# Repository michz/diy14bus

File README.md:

diy14bus
========

Getting started
---------------
Please read [Erste (Repository-)Schritte](http://michz.github.io/diy14bus/2014/12/Erste-Repo-Schritte/) (german).

Short version in english:
Please make sure that you have cloned
[our RIOT fork](https://github.com/patkan/RIOT) on the same directory level.

Example:

    /home/user/home-project/diy14bus/   # this repository
    /home/user/home-project/RIOT/       # patkan/RIOT

For compiling arm based binaries you need a fully functional arm-gcc toolchain.
We use [gcc-arm-embedded](https://launchpad.net/~terry.guo/+archive/ubuntu/gcc-arm-embedded).

If you want to run the configuration tool on a Raspberry Pi,
clone the
[RF24](https://github.com/TMRh20/RF24/tree/interrupts)-
Repository and the 
[WebsocketPP](https://github.com/zaphoyd/websocketpp.git)-
Repository into a directory on the same level as the above mentioned.

Your final directory structure should look like this:

    your_project_dir
    |--> diy14bus/
    |--> RIOT/
    |--> RF24/
    |--> websocketpp/

Compiling
---------
Go to application directory (for example `first-test/`) and run `make`.
(No need to build RIOT directly.)

Compiling cowbus-config-server
------------------------------
One special note about the config-server:
This tool depends on a Raspberry Pi and can be compiled there, and *only there*.
(Fancy crosscompiling voodoo possible...)

Before being able to compile cowbus-config-server, you have to compile and install
the RF24 library by changing to the directory RF24 and type:

    make install   # NOTE: perhaps you need sudo ...

This compiles the RF24 library and installs the binary system wide.

Moreover you need at least GCC version 4.7 or 4.8 (we use C++11 language features).

You need Boost library: System, IOStreams, Thread.
On Raspbian you can simply do:

    apt-get install libboost-system-dev libboost-iostreams-dev libboost-thread-dev

License
-------
We will think about it.

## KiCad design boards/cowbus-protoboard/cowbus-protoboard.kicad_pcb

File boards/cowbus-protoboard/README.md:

cowbus protoboard - a prototyping board
=======================================

Core components
---------------
* CPU: [STM32F030C8T6]
* Radio: nrf24l01+
* LDO: [TS5204]
* EEPROM: [24LC04B-I/SN]

On periphery board:
* Temperatur Sensor: [LM 75]
* Buzzer: Some piezo that does not draw more than 25mA and works with 3,3V,
    for example: [EKULIT SMD-P16]
* LED: [LRTB G6TG]

I2C-Bus
-------

This board provides a I2C bus.
Following addresses are reserved:

* 1010xxx (serial EEPROM; where x is either 1 or 0)
* 1001000 (temperature sensor on periphery board)

License
-------
This board is licensed under
[Creative Commons Attribution 4.0 International (CC BY 4.0)](https://creativecommons.org/licenses/by/4.0/)

[STM32F030C8T6]: http://www.digikey.de/product-detail/de/STM32F030C8T6/497-14043-ND/4357252

[EKULIT SMD-P16]: https://www.reichelt.de/Signalakustik/SMD-P16/3/index.html?ACTION=3&GROUPID=6560&ARTICLE=145909&OFFSET=500&WKID=0&
[LM 75]: https://www.reichelt.de/Temperatursensoren/LM-75-SMD/3/index.html?ACTION=3&GROUPID=6672&ARTICLE=49349&SEARCH=i2c%20temperatur%20sensor&OFFSET=500&WKID=0&
[TS5204]: https://www.reichelt.de/ICs-TLC-TSA-/TS-5204-CX33/3/index.html?ACTION=3&GROUPID=5480&ARTICLE=115980&OFFSET=500&WKID=0&
[24LC04B-I/SN]: https://www.reichelt.de/EEPROM-seriell-Microchip/24LC04B-I-SN/3/index.html?ACTION=3&GROUPID=4511&ARTICLE=40074&OFFSET=500&WKID=0&
[LRTB G6TG]: https://www.reichelt.de/SMD-LEDs-Multi-Color/LRTB-G6TG/3/index.html?ACTION=3&GROUPID=3036&ARTICLE=65109&OFFSET=500&WKID=0&

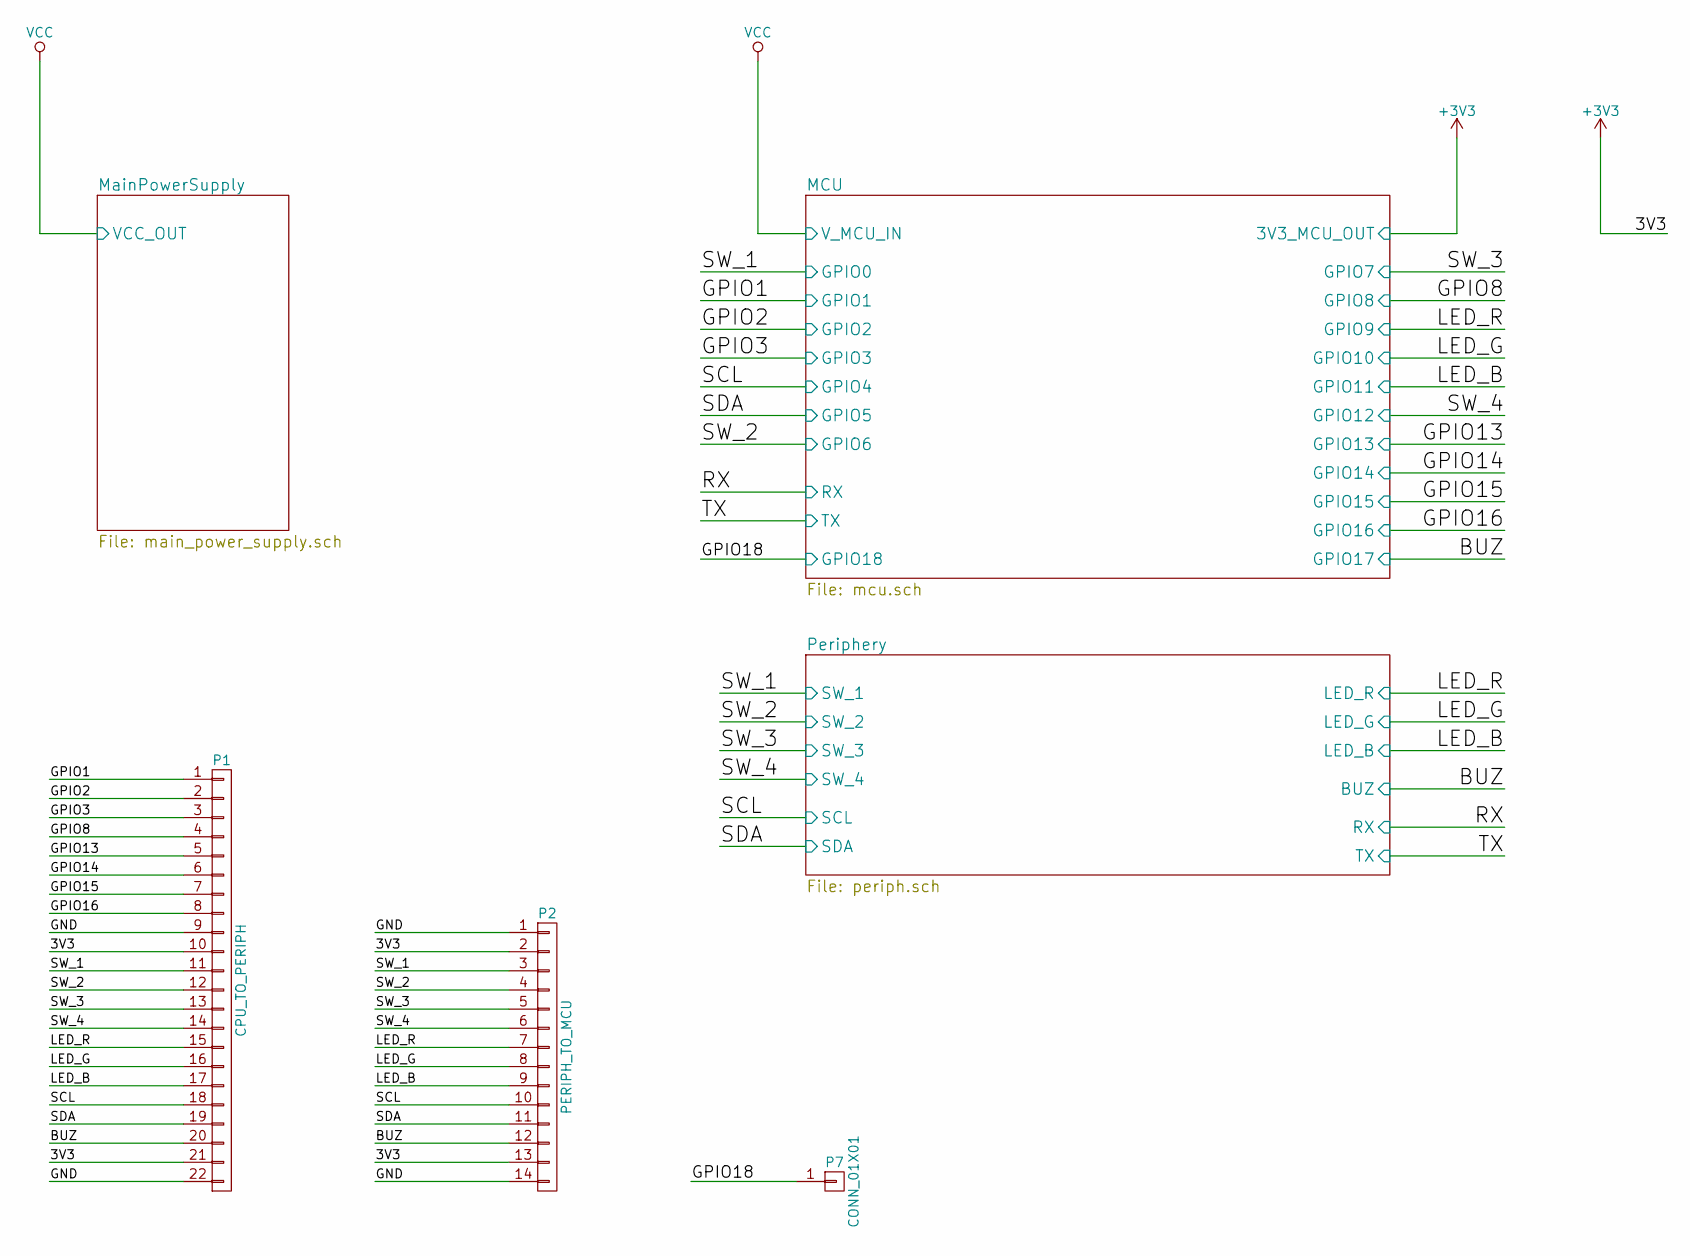
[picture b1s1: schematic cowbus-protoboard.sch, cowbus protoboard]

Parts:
P1: CPU_TO_PERIPH; Pin_Header_Straight_1x22
P2: PERIPH_TO_MCU; Pin_Header_Straight_1x14
P7: CONN_01X01; Pin_Header_Straight_1x01

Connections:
+3V3: P1.10, P1.21, P2.2, P2.13; also elsewhere on the board
/MCU/GPIO0: P1.11, P2.3; also elsewhere on the board
/MCU/GPIO1: P1.1; also elsewhere on the board
/MCU/GPIO2: P1.2; also elsewhere on the board
/MCU/GPIO3: P1.3; also elsewhere on the board
/MCU/GPIO4: P1.18, P2.10; also elsewhere on the board
/MCU/GPIO5: P1.19, P2.11; also elsewhere on the board
/MCU/GPIO6: P1.12, P2.4; also elsewhere on the board
/MCU/GPIO7: P1.13, P2.5; also elsewhere on the board
/MCU/GPIO8: P1.4; also elsewhere on the board
/MCU/GPIO9: P1.15, P2.7; also elsewhere on the board
/MCU/GPIO10: P1.16, P2.8; also elsewhere on the board
/MCU/GPIO11: P1.17, P2.9; also elsewhere on the board
/MCU/GPIO12: P1.14, P2.6; also elsewhere on the board
/MCU/GPIO13: P1.5; also elsewhere on the board
/MCU/GPIO14: P1.6; also elsewhere on the board
/MCU/GPIO15: P1.7; also elsewhere on the board
/MCU/GPIO16: P1.8; also elsewhere on the board
/Periphery/BUZ: P1.20, P2.12; also elsewhere on the board
GND: P1.9, P1.22, P2.1, P2.14; also elsewhere on the board

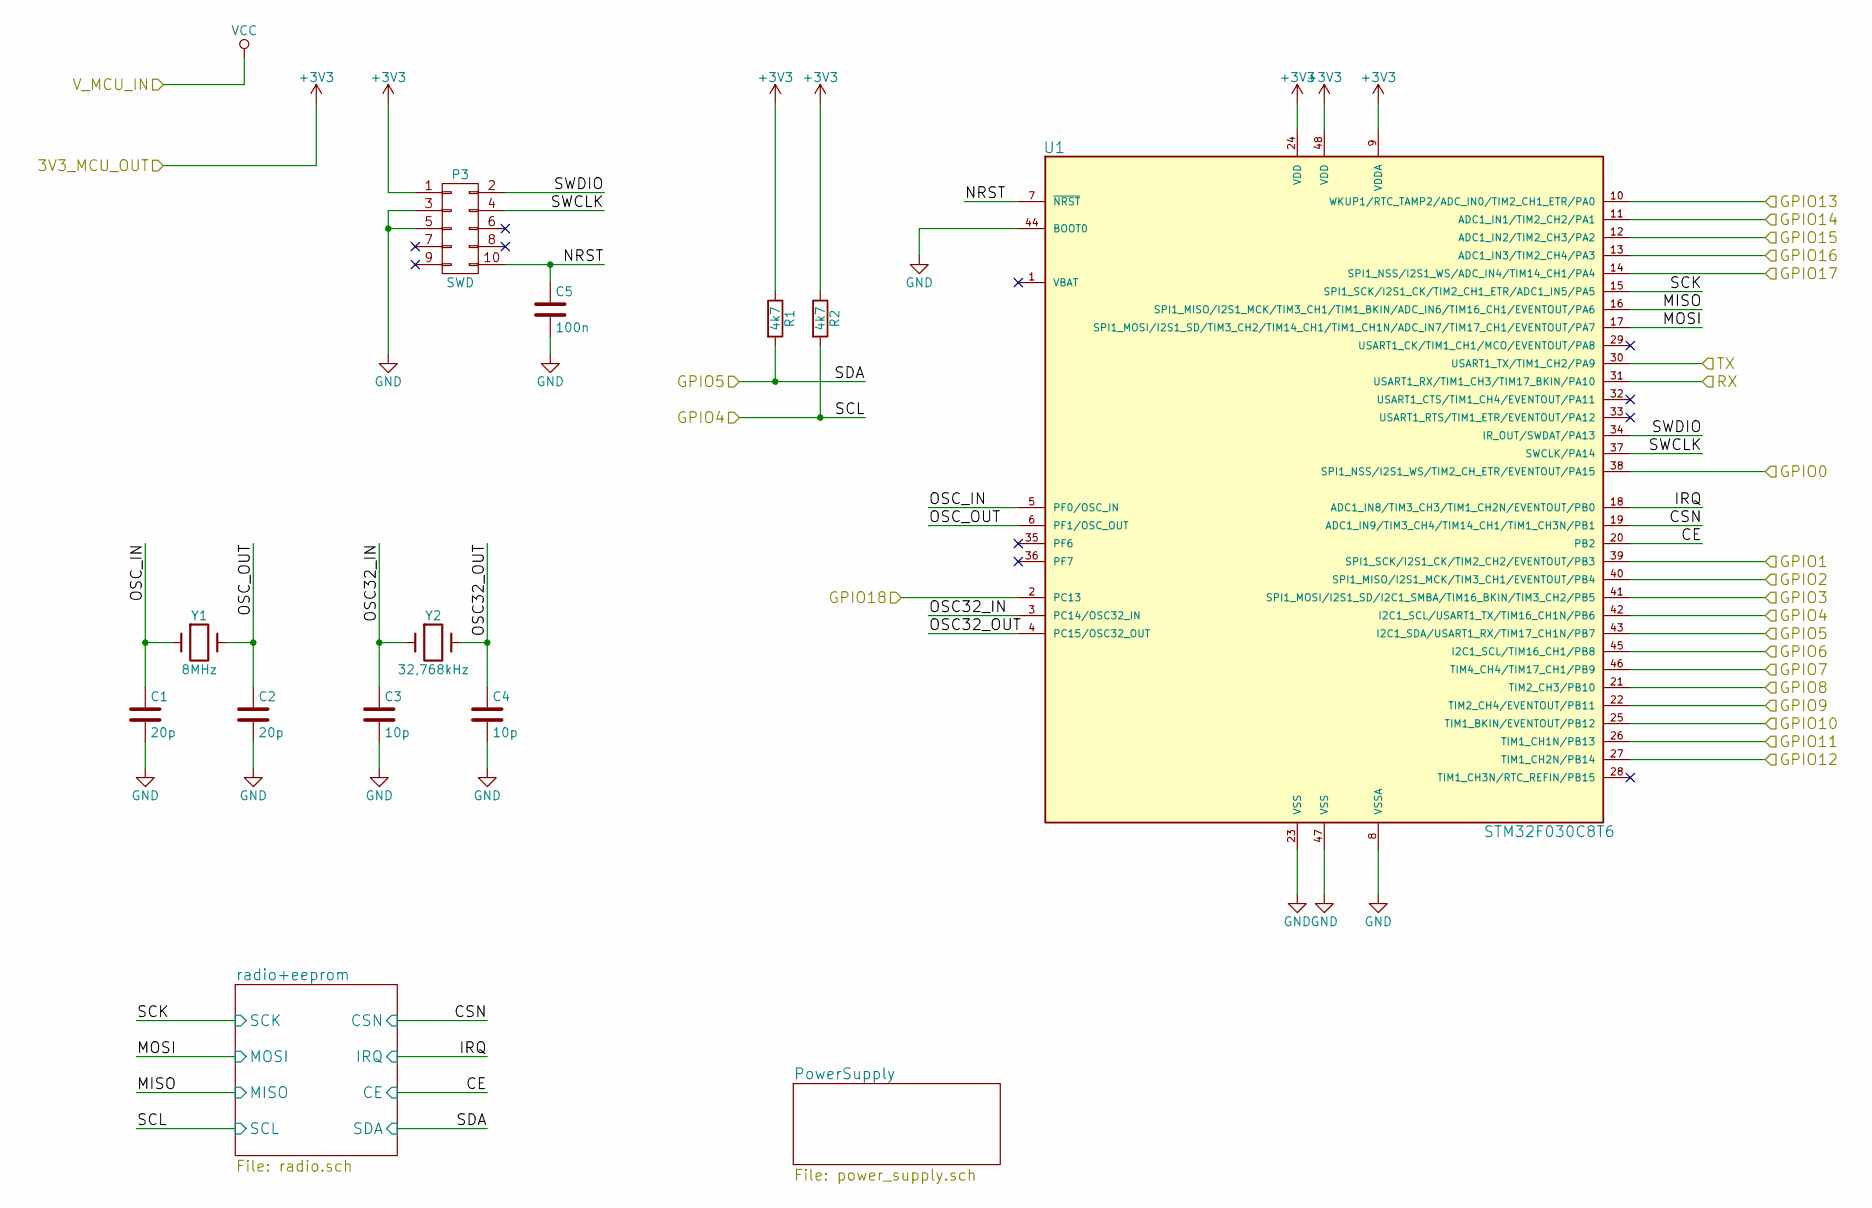
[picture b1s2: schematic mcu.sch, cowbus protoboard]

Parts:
C1, C2: 20p; C_0805_HandSoldering
C3, C4: 10p; C_0805_HandSoldering
C5: 100n; C_0805_HandSoldering
P3: SWD; CORTEX_header_SMD
R1, R2: 4k7; R_0805_HandSoldering
U1: STM32F030C8T6; LQFP-48_7x7mm_Pitch0.5mm
Y1: 8MHz; Crystal_HC49-SD_SMD
Y2: 32,768kHz; crystal_SMD_CPFB

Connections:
+3V3: P3.1, R1.1, R2.1, U1.9 (VDDA), U1.24 (VDD), U1.48 (VDD); also elsewhere on the board
/MCU/GPIO0: U1.38 (SPI1_NSS/I2S1_WS/TIM2_CH_ETR/EVENTOUT/P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); also elsewhere on the board
/MCU/GPIO1: U1.39 (SPI1_SCK/I2S1_CK/TIM2_CH2/EVENTOUT/PB3); also elsewhere on the board
/MCU/GPIO2: U1.40 (SPI1_MISO/I2S1_MCK/TIM3_CH1/EVENTOUT/PB4); also elsewhere on the board
/MCU/GPIO3: U1.41 (SPI1_MOSI/I2S1_SD/I2C1_SMBA/TIM16_BKIN/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); also elsewhere on the board
/MCU/GPIO4: R2.2, U1.42 (I2C1_SCL/USART1_TX/TIM16_CH1N/PB6); also elsewhere on the board
/MCU/GPIO5: R1.2, U1.43 (I2C1_SDA/USART1_RX/TIM17_CH1N/PB7); also elsewhere on the board
/MCU/GPIO6: U1.45 (I2C1_SCL/TIM16_CH1/PB8); also elsewhere on the board
/MCU/GPIO7: U1.46 (TIM4_CH4/TIM17_CH1/PB9); also elsewhere on the board
/MCU/GPIO8: U1.21 (TIM2_CH3/PB10); also elsewhere on the board
/MCU/GPIO9: U1.22 (TIM2_CH4/EVENTOUT/PB11); also elsewhere on the board
/MCU/GPIO10: U1.25 (TIM1_BKIN/EVENTOUT/PB12); also elsewhere on the board
/MCU/GPIO11: U1.26 (TIM1_CH1N/PB13); also elsewhere on the board
/MCU/GPIO12: U1.27 (TIM1_CH2N/PB14); also elsewhere on the board
/MCU/GPIO13: U1.10 (WKUP1/RTC_TAMP2/ADC_IN0/TIM2_CH1_ETR/PA0); also elsewhere on the board
/MCU/GPIO14: U1.11 (ADC1_IN1/TIM2_CH2/PA1); also elsewhere on the board
/MCU/GPIO15: U1.12 (ADC1_IN2/TIM2_CH3/PA2); also elsewhere on the board
/MCU/GPIO16: U1.13 (ADC1_IN3/TIM2_CH4/PA3); also elsewhere on the board
/MCU/GPIO18: U1.2 (PC13); also elsewhere on the board
/MCU/NRST: C5.1, P3.10, U1.7 (~NRST)
/MCU/OSC32_IN: C3.1, U1.3 (PC14/OSC32_IN), Y2.1
/MCU/OSC32_OUT: C4.1, U1.4 (PC15/OSC32_OUT), Y2.2
/MCU/OSC_IN: C1.1, U1.5 (PF0/OSC_IN), Y1.1
/MCU/OSC_OUT: C2.1, U1.6 (PF1/OSC_OUT), Y1.2
/MCU/RX: U1.31 (USART1_RX/TIM1_CH3/TIM17_BKIN/PA10); also elsewhere on the board
/MCU/SWCLK: P3.4, U1.37 (SWCLK/PA14)
/MCU/SWDIO: P3.2, U1.34 (IR_OUT/SWDAT/PA13)
/MCU/TX: U1.30 (USART1_TX/TIM1_CH2/PA9); also elsewhere on the board
/MCU/radio+eeprom/CE: U1.20 (PB2); also elsewhere on the board
/MCU/radio+eeprom/CSN: U1.19 (ADC1_IN9/TIM3_CH4/TIM14_CH1/TIM1_CH3N/P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); also elsewhere on the board
/MCU/radio+eeprom/IRQ: U1.18 (ADC1_IN8/TIM3_CH3/TIM1_CH2N/EVENTOUT/PB0); also elsewhere on the board
/MCU/radio+eeprom/MISO: U1.16 (SPI1_MISO/I2S1_MCK/TIM3_CH1/TIM1_BKIN/A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); also elsewhere on the board
/MCU/radio+eeprom/MOSI: U1.17 (SPI1_MOSI/I2S1_SD/TIM3_CH2/TIM14_CH1/TI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); also elsewhere on the board
/MCU/radio+eeprom/SCK: U1.15 (SPI1_SCK/I2S1_CK/TIM2_CH1_ETR/ADC1_IN5/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); also elsewhere on the board
/Periphery/BUZ: U1.14 (SPI1_NSS/I2S1_WS/ADC_IN4/TIM14_CH1/PA4); also elsewhere on the board
GND: C1.2, C2.2, C3.2, C4.2, C5.2, P3.3, P3.5, U1.8 (VSSA), U1.23 (VSS), U1.44 (BOOT0), U1.47 (VSS); also elsewhere on the board

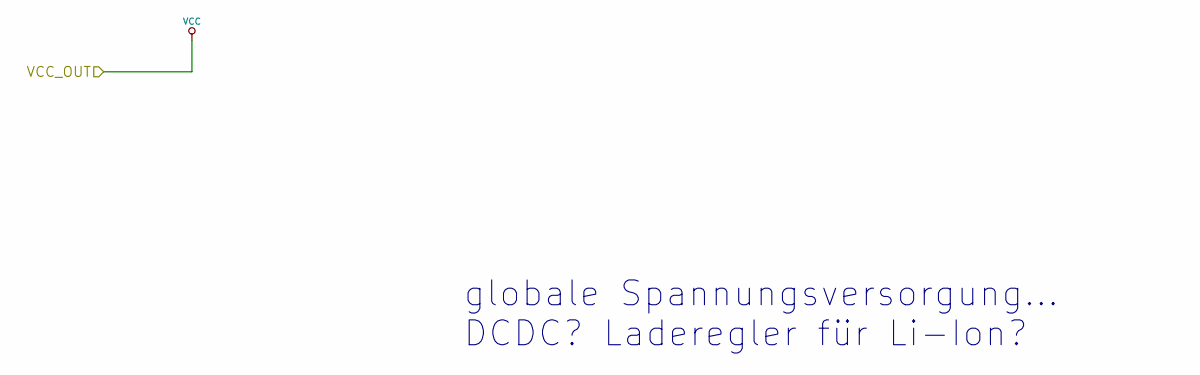
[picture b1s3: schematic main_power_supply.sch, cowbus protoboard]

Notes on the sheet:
globale Spannungsversorgung... DCDC? Laderegler für Li-Ion?

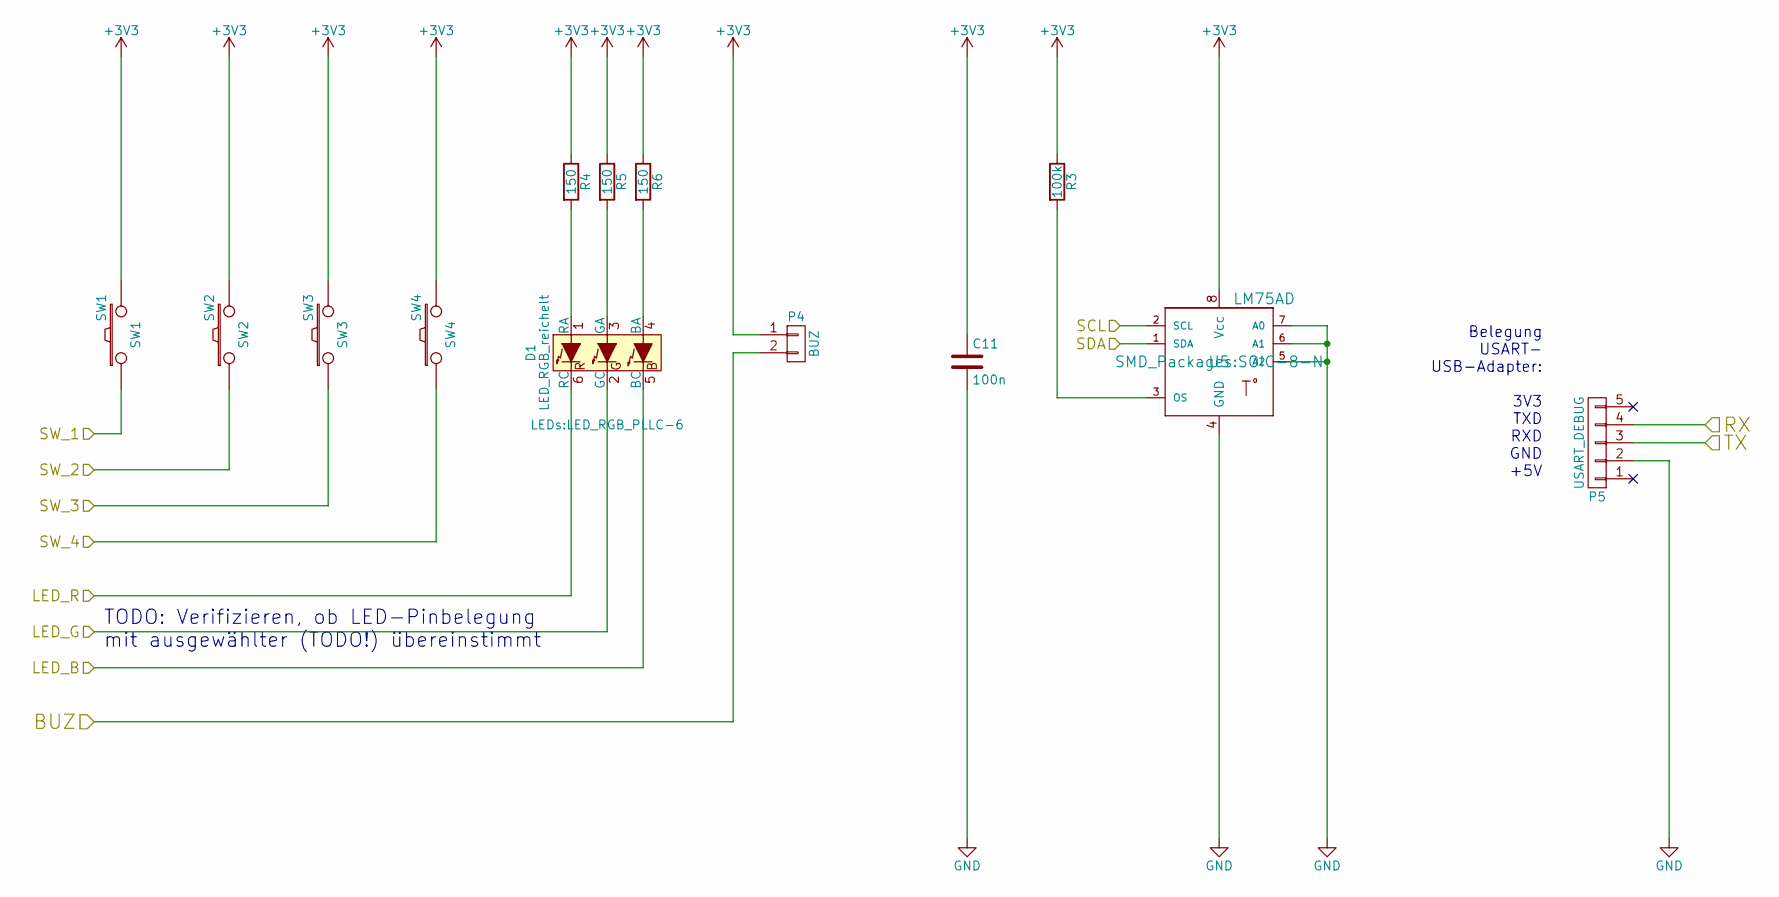
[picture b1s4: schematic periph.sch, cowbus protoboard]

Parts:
C11: 100n; C_0805_HandSoldering
D1: LED_RGB_reichelt; LED_RGB_PLLC-6
P4: BUZ; Pin_Header_Straight_1x02
P5: USART_DEBUG; Pin_Header_Straight_1x05
R3: 100k; R_0805_HandSoldering
R4, R5, R6: 150; R_0805_HandSoldering
SW1: SW1; Button_SMD_Schurter_LSG
SW2: SW2; Button_SMD_Schurter_LSG
SW3: SW3; Button_SMD_Schurter_LSG
SW4: SW4; Button_SMD_Schurter_LSG
U5: LM75AD; SOIC-8-N

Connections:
+3V3: C11.1, P4.1, R3.1, R4.1, R5.1, R6.1, SW1.2, SW2.2, SW3.2, SW4.2, U5.8 (Vcc); also elsewhere on the board
/MCU/GPIO0: SW1.1; also elsewhere on the board
/MCU/GPIO4: U5.2 (SCL); also elsewhere on the board
/MCU/GPIO5: U5.1 (SDA); also elsewhere on the board
/MCU/GPIO6: SW2.1; also elsewhere on the board
/MCU/GPIO7: SW3.1; also elsewhere on the board
/MCU/GPIO9: D1.6 (RC); also elsewhere on the board
/MCU/GPIO10: D1.2 (GC); also elsewhere on the board
/MCU/GPIO11: D1.5 (BC); also elsewhere on the board
/MCU/GPIO12: SW4.1; also elsewhere on the board
/MCU/RX: P5.4; also elsewhere on the board
/MCU/TX: P5.3; also elsewhere on the board
/Periphery/BUZ: P4.2; also elsewhere on the board
GND: C11.2, P5.2, U5.4 (GND), U5.5 (A2), U5.6 (A1), U5.7 (A0); also elsewhere on the board
unnamed: D1.1 (RA), R4.2
unnamed: D1.3 (GA), R5.2
unnamed: D1.4 (BA), R6.2
unnamed: R3.2, U5.3 (OS)

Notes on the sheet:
TODO: Verifizieren, ob LED-Pinbelegung mit ausgewählter (TODO!) übereinstimmt
Belegung USART- USB-Adapter: 3V3 TXD RXD GND +5V

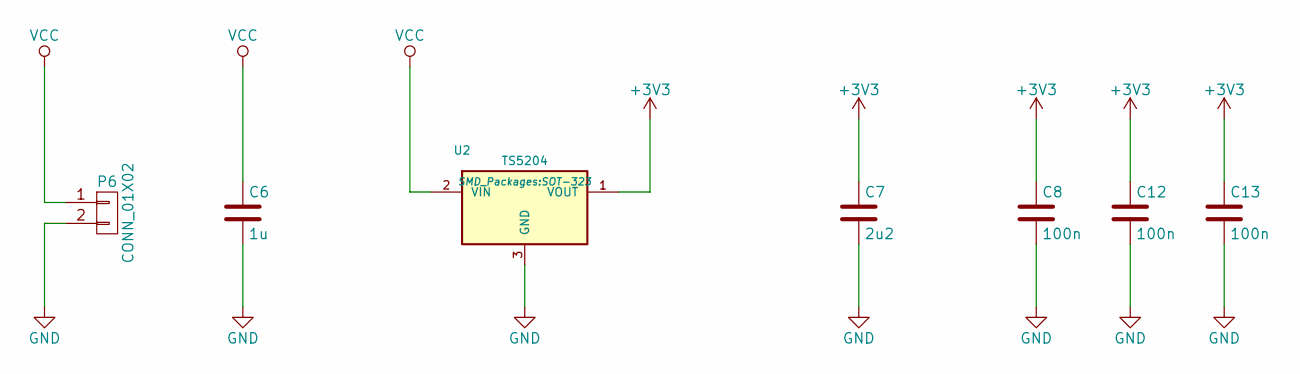
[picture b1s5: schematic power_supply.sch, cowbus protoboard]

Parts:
C6: 1u; C_0805_HandSoldering
C7: 2u2; C_0805_HandSoldering
C8, C12, C13: 100n; C_0805_HandSoldering
P6: CONN_01X02; Pin_Header_Straight_1x02
U2: TS5204; SOT-323

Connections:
+3V3: C7.1, C8.1, C12.1, C13.1, U2.1 (VOUT); also elsewhere on the board
GND: C6.2, C7.2, C8.2, C12.2, C13.2, P6.2, U2.3 (GND); also elsewhere on the board
VCC: C6.1, P6.1, U2.2 (VIN)

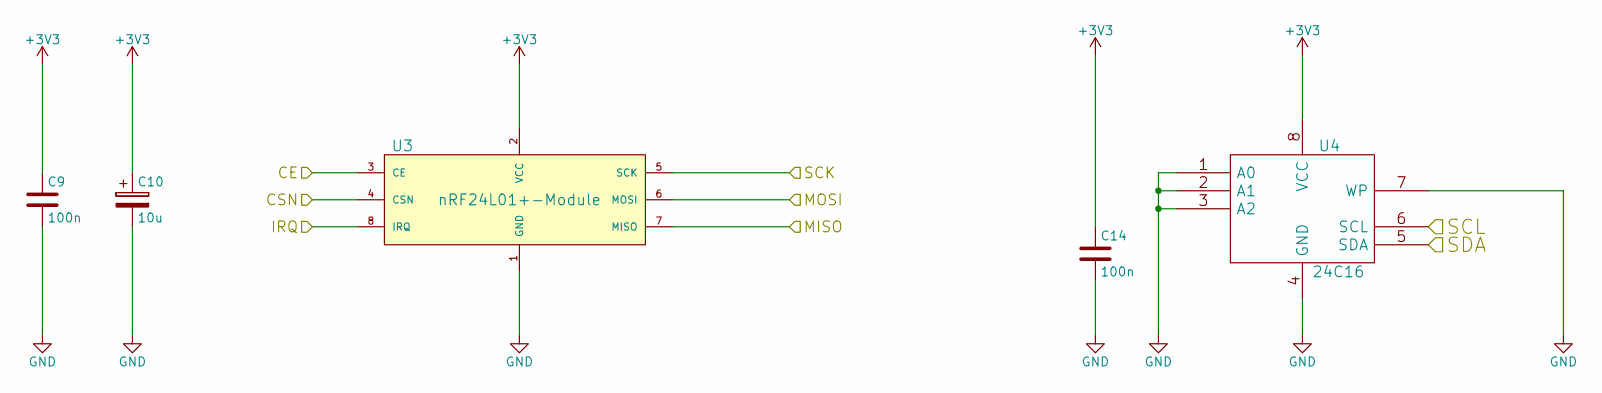
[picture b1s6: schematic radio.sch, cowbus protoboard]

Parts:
C9, C14: 100n; C_0805_HandSoldering
C10: 10u; c_elec_4x5.8
U3: nRF24L01+-Module; Pin_Header_Straight_2x05
U4: 24C16; SOIC-8-N

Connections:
+3V3: C9.1, C10.1, C14.1, U3.2 (VCC), U4.8 (VCC); also elsewhere on the board
/MCU/GPIO4: U4.6 (SCL); also elsewhere on the board
/MCU/GPIO5: U4.5 (SDA); also elsewhere on the board
/MCU/radio+eeprom/CE: U3.3 (CE); also elsewhere on the board
/MCU/radio+eeprom/CSN: U3.4 (CSN); also elsewhere on the board
/MCU/radio+eeprom/IRQ: U3.8 (IRQ); also elsewhere on the board
/MCU/radio+eeprom/MISO: U3.7 (MISO); also elsewhere on the board
/MCU/radio+eeprom/MOSI: U3.6 (MOSI); also elsewhere on the board
/MCU/radio+eeprom/SCK: U3.5 (SCK); also elsewhere on the board
GND: C9.2, C10.2, C14.2, U3.1 (GND), U4.1 (A0), U4.2 (A1), U4.3 (A2), U4.4 (GND), U4.7 (WP); also elsewhere on the board

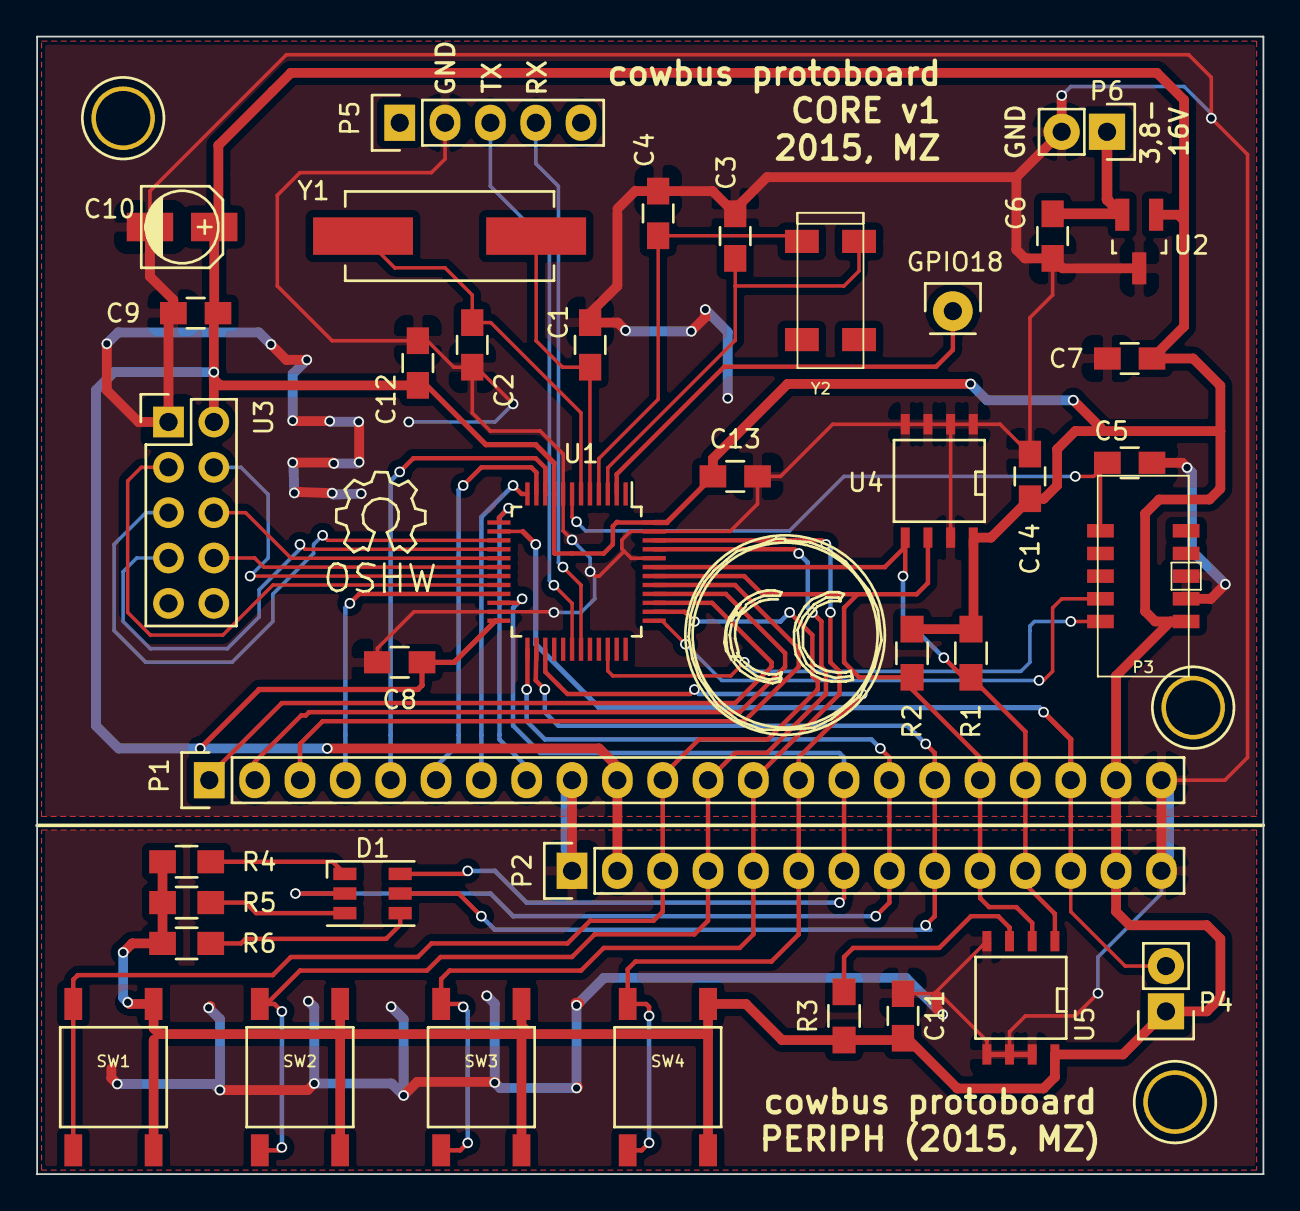
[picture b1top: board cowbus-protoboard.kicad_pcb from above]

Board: 2 copper layers, 68.7 x 63.7 mm, 39 parts (0 on the bottom side), 41 nets.

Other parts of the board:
GPIO18: CONN_01X01; Pin_Header_Straight_1x01

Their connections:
/MCU/GPIO18: GPIO18.1; also elsewhere on the board

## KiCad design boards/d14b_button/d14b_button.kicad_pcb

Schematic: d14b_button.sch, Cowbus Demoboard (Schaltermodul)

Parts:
BT1: BATTERY; KZH20SMD-2
C1, C3, C4, C6, C12, C14, C17: 100n; C_0603
C2: 10u; c_elec_4x5.8
C5: 4.7u; c_elec_4x5.8
C7: 10n; C_0603
C8: 1u; C_0603
C9, C10: 20p; C_0603
C11, C13: 10p; C_0603
C15, C16: 10u; C_0805
CON1: USB-MICRO-B; USB_Micro-B
D1: LED_RABG; PLCC-4
D2: LED; LED-0603
D3, D4, D5, D6: Z5V1; Diode-MiniMELF_Standard
D7: DIODE; Diode-MiniMELF_Standard
D8: ZENERsmall; Diode-MiniMELF_Standard
JP1, JP2, JP3: JUMPER3; PINHEAD1-3
JP4, JP5, JP6: JUMPER; PINHEAD1-2
L1: 4.7u; NRS8030
P1: CONN_02X05; CORTEX_header_SMD
P2: CONN_01X03; PINHEAD1-3
P3: PIEZO_BUZZ; PINHEAD1-2
P4: EEPROM_SPI; MSOP-8
Q1: MOSFET_N; SOT-23-GDS
Q2: IRLM6402; SOT-23-GDS
Q3: BSS138; SOT-23-GDS
R1: 100k; R_0603
R2, R5, R6: 680; R_0603
R3: 510; R_0603
R4, R7, R8, R9, R14, R15: 10k; R_0603
R10, R12: 0; R_0603
R11: 10, 2.5W; Resistor_Horizontal_RM20mm
R13: *; R_0603
SW1, SW2, SW3, SW4: SW_PUSH; Button_SMD_Schurter_LSG
U1: nRF24L01+-Module; Pin_Header_Straight_2x04
U2: STM32F030C8T6; LQFP-48_7x7mm_Pitch0.5mm
U3: TPS61221; SC70-6
X1: 8M; Crystal_HC49-SD_SMD
X2: 32.768k; crystal_SMD_CPFB

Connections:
+3V3: C3.1, C4.1, C5.1, C6.1, C7.1, C8.1, C14.1, D1.2, D3.2 (A), D7.2 (K), JP1.3, JP2.3, JP4.1, JP6.2, P1.1, P3.1, P4.8, R8.1, R9.1, SW1.2, SW2.2, SW4.2, U2.1 (VBAT), U2.9 (VDDA), U2.24 (VDD), U2.48 (VDD)
/CE: U1.3 (CE), U2.20 (PB2)
/CSN: U1.4 (CSN), U2.19 (ADC1_IN9/TIM3_CH4/TIM14_CH1/TIM1_CH3N/P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)
/DIV_MEAS: C17.1, D8.2 (A), R14.2, R15.1, U2.14 (SPI1_NSS/I2S1_WS/ADC_IN4/TIM14_CH1/PA4)
/IRQ: U1.8 (IRQ), U2.18 (ADC1_IN8/TIM3_CH3/TIM1_CH2N/EVENTOUT/PB0)
/MEAS_ENABLE: Q3.G, U2.29 (USART1_CK/TIM1_CH1/MCO/EVENTOUT/PA8)
/MISO: P4.2, U1.7 (MISO), U2.16 (SPI1_MISO/I2S1_MCK/TIM3_CH1/TIM1_BKIN/A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)
/MOSI: P4.5, U1.6 (MOSI), U2.17 (SPI1_MOSI/I2S1_SD/TIM3_CH2/TIM14_CH1/TI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)
/NRST: C12.2, D6.2 (A), P1.10, R9.2, SW3.1, U2.7 (~NRST)
/ROM_CS: P4.1, U2.21 (TIM2_CH3/PB10)
/ROM_HOLD: P4.7, U2.22 (TIM2_CH4/EVENTOUT/PB11)
/SCK: P4.6, U1.5 (SCK), U2.15 (SPI1_SCK/I2S1_CK/TIM2_CH1_ETR/ADC1_IN5/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)
/SWCLK: D5.2 (A), P1.4, R7.1, U2.37 (SWCLK/PA14)
/SWDIO: D4.2 (A), P1.2, R8.2, U2.34 (IR_OUT/SWDAT/PA13)
/UARTRX: P2.1, U2.31 (USART1_RX/TIM1_CH3/TIM17_BKIN/PA10)
/UARTTX: P2.2, U2.30 (USART1_TX/TIM1_CH2/PA9)
/VSUP_MEAS: JP3.2, JP5.1, Q2.S, R1.1
GND: BT1.2 (-), C1.2, C2.2, C3.2, C4.2, C5.2, C6.2, C7.2, C8.2, C9.1, C10.1, C11.2, C12.1, C13.2, C14.2, C15.2, C16.2, C17.2, D2.2 (A), D3.1 (K), D4.1 (K), D5.1 (K), D6.1 (K), D8.1 (K), JP1.1, JP2.1, P1.3, P1.5, P2.3, P4.4, Q1.S, Q3.S, R7.2, R11.1, R13.2, R15.2, SW3.2, U1.1 (GND), U2.8 (VSSA), U2.23 (VSS), U2.47 (VSS), U3.3 (GND); also elsewhere on the board
unnamed: BT1.1 (+), JP3.1
unnamed: C1.1, C2.1, JP4.2, U1.2 (VCC)
unnamed: C9.2, U2.5 (PF0/OSC_IN), X1.2
unnamed: C10.2, R10.1, X1.1
unnamed: C11.1, U2.3 (PC14/OSC32_IN), X2.2
unnamed: C13.1, U2.4 (PC15/OSC32_OUT), X2.1
unnamed: C15.1, JP5.2, L1.1, U3.1 (VIN), U3.6 (EN)
unnamed: C16.1, JP6.1, R12.1, U3.4 (VOUT)
unnamed: CON1.5 (GND), R11.2
unnamed: D1.1, R2.1
unnamed: D1.3, R5.1
unnamed: D1.4, R3.1
unnamed: D2.1 (K), R6.1
unnamed: D7.1 (A), P3.2, Q1.D
unnamed: JP1.2, R4.2
unnamed: JP2.2, P4.3
unnamed: L1.2, U3.5 (L)
unnamed: Q1.G, U2.26 (TIM1_CH1N/PB13)
unnamed: Q2.D, R14.1
unnamed: Q2.G, Q3.D, R1.2
unnamed: R2.2, U2.10 (WKUP1/RTC_TAMP2/ADC_IN0/TIM2_CH1_ETR/PA0)
unnamed: R3.2, U2.11 (ADC1_IN1/TIM2_CH2/PA1)
unnamed: R4.1, U2.44 (BOOT0)
unnamed: R5.2, U2.12 (ADC1_IN2/TIM2_CH3/PA2)
unnamed: R6.2, U2.13 (ADC1_IN3/TIM2_CH4/PA3)
unnamed: R10.2, U2.6 (PF1/OSC_OUT)
unnamed: R12.2, R13.1, U3.2 (FB)
unnamed: SW1.1, U2.40 (SPI1_MISO/I2S1_MCK/TIM3_CH1/EVENTOUT/PB4)
unnamed: SW2.1, U2.41 (SPI1_MOSI/I2S1_SD/I2C1_SMBA/TIM16_BKIN/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)
unnamed: SW4.1, U2.45 (I2C1_SCL/TIM16_CH1/PB8)

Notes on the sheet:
STM32F0
NRF24L01
SWD
PSU
UART
RESET-BTN
EEPROM über SPI
Pinbelegung: 1 #CS 2 SO 3 #WP 4 VSS 5 VCC 6 #HOLD 7 SCK 8 SI Chip: 25AA640AT-I/MS (64K von Digikey)
auf high setzen
Pull-Up Pull-Down
VSUP-Messung

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
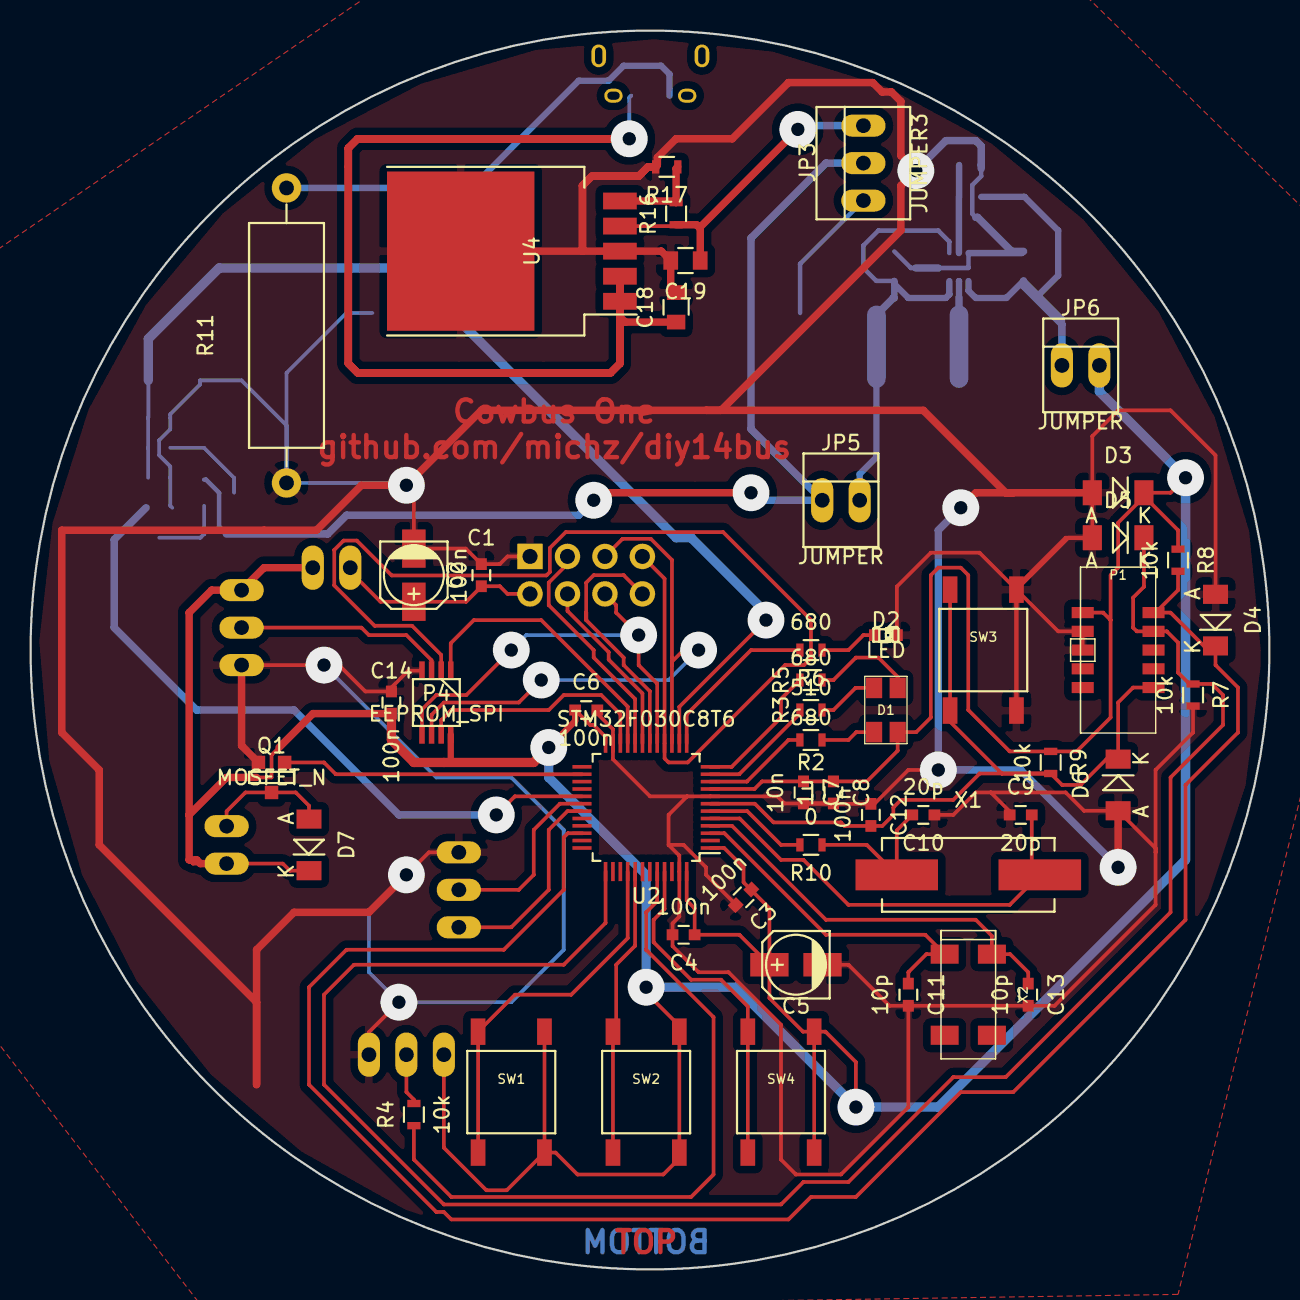
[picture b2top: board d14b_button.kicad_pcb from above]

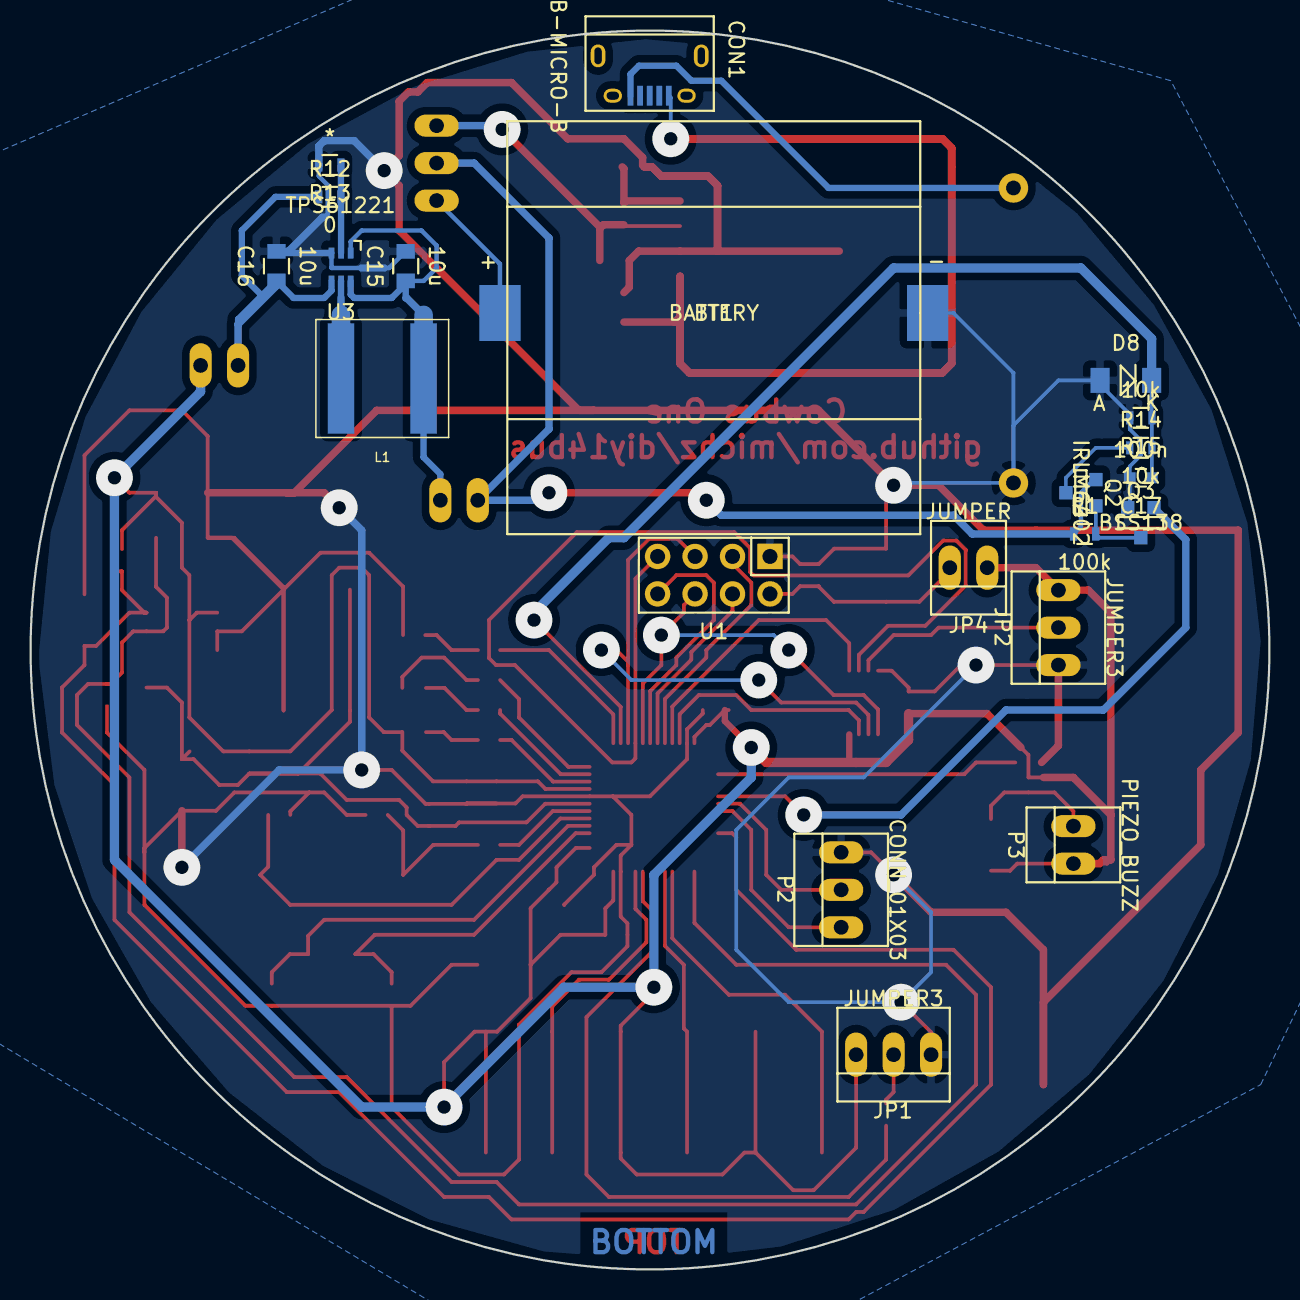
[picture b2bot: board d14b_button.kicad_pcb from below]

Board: 2 copper layers, 84.0 x 84.0 mm, 70 parts (21 on the bottom side), 51 nets.

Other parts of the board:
C18, C19: 10u; C_0805
R16, R17: *; R_0603
U4: LP38502-ADJ; TO-263-5

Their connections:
GND: C18.2, C19.2, R17.2, U4.3; also elsewhere on the board
unnamed: R16.2, R17.1, U4.5
